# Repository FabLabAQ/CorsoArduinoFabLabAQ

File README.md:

# Corso Arduino FabLab AQ
1° Corso Arduino organizzato dal FabLab L'Aquila
<br>Questa repository contiene gli sketch del corso e gli schemi
<br>Inoltre potete trovare anche i progetti del robot

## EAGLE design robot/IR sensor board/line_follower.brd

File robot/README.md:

# Robot line-follower
Qui trovate i disegni e il modello 3D del robottino line-follower usato nel corso

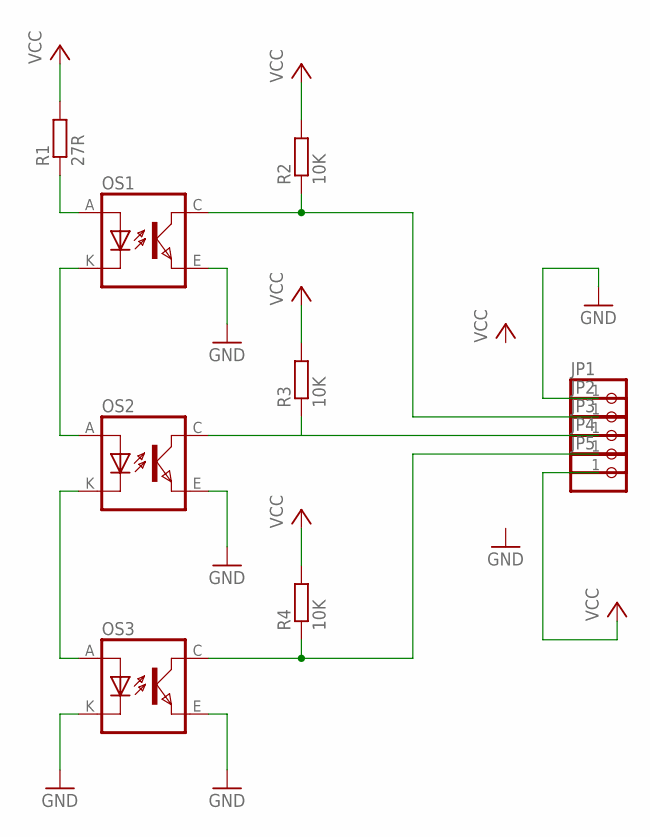
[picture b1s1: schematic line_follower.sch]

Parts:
JP1, JP2, JP3, JP4, JP5: PINHD-1X1; 1X01
OS1, OS2, OS3: TCRT5000
R1: 27R; 0204/7
R2, R3, R4: 10K; 0204/7

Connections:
GND: JP1.1, OS1.E (EMITTER), OS2.E (EMITTER), OS3.E (EMITTER), OS3.K (CATHODE)
unnamed: OS1.K (CATHODE), OS2.A (ANODE)
unnamed: OS2.K (CATHODE), OS3.A (ANODE)
unnamed: OS1.A (ANODE), R1.1
unnamed: JP2.1, OS1.C (COLLECTOR), R2.1
unnamed: JP3.1, OS2.C (COLLECTOR), R3.1
unnamed: JP4.1, OS3.C (COLLECTOR), R4.1
VCC: JP5.1, R1.2, R2.2, R3.2, R4.2

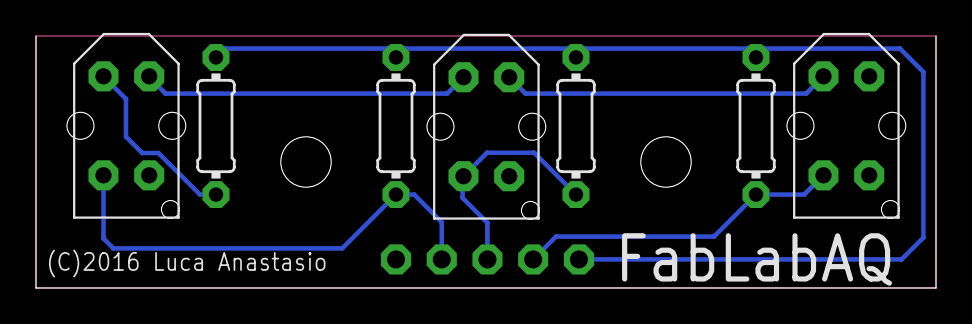
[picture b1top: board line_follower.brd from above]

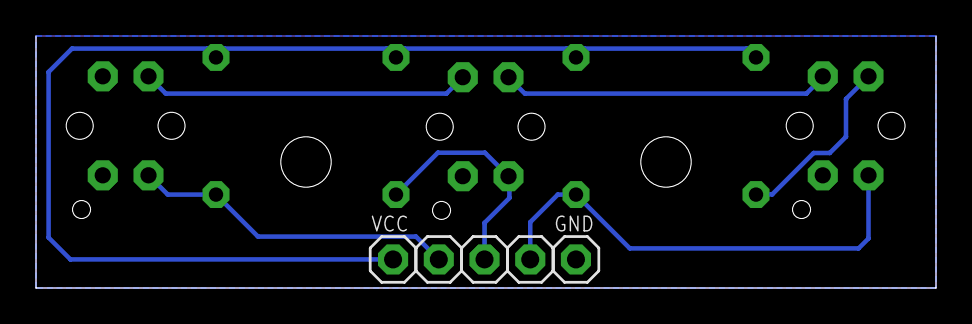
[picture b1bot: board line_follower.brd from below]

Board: 2 copper layers, 50.0 x 14.0 mm, 12 parts (5 on the bottom side), 8 nets.

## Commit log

2016-02-11 sketch00
2016-02-11 more sketches
2016-02-15 new folder structure
2016-02-15 robot drawings
2016-02-19 add readme
2016-02-19 add ir sensor board
2016-02-20 update sketch index
2016-02-21 update naming scheme
2016-02-22 TEST
    Prova inserimento commenti.
2016-02-22 add some comments
2016-02-22 new sketches
2016-03-10 updated sketch index
2016-08-07 updated robot drawings
2016-08-07 updated schematic and board
2016-08-07 added stl for 3D print
2016-10-23 new motor holder
2016-10-25 README
2016-10-25 updated python scripts
2016-11-10 new sketch
2016-11-27 updated sensor board

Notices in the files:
robot/IR sensor board/line_follower.brd:
(C)2016 Luca Anastasio
